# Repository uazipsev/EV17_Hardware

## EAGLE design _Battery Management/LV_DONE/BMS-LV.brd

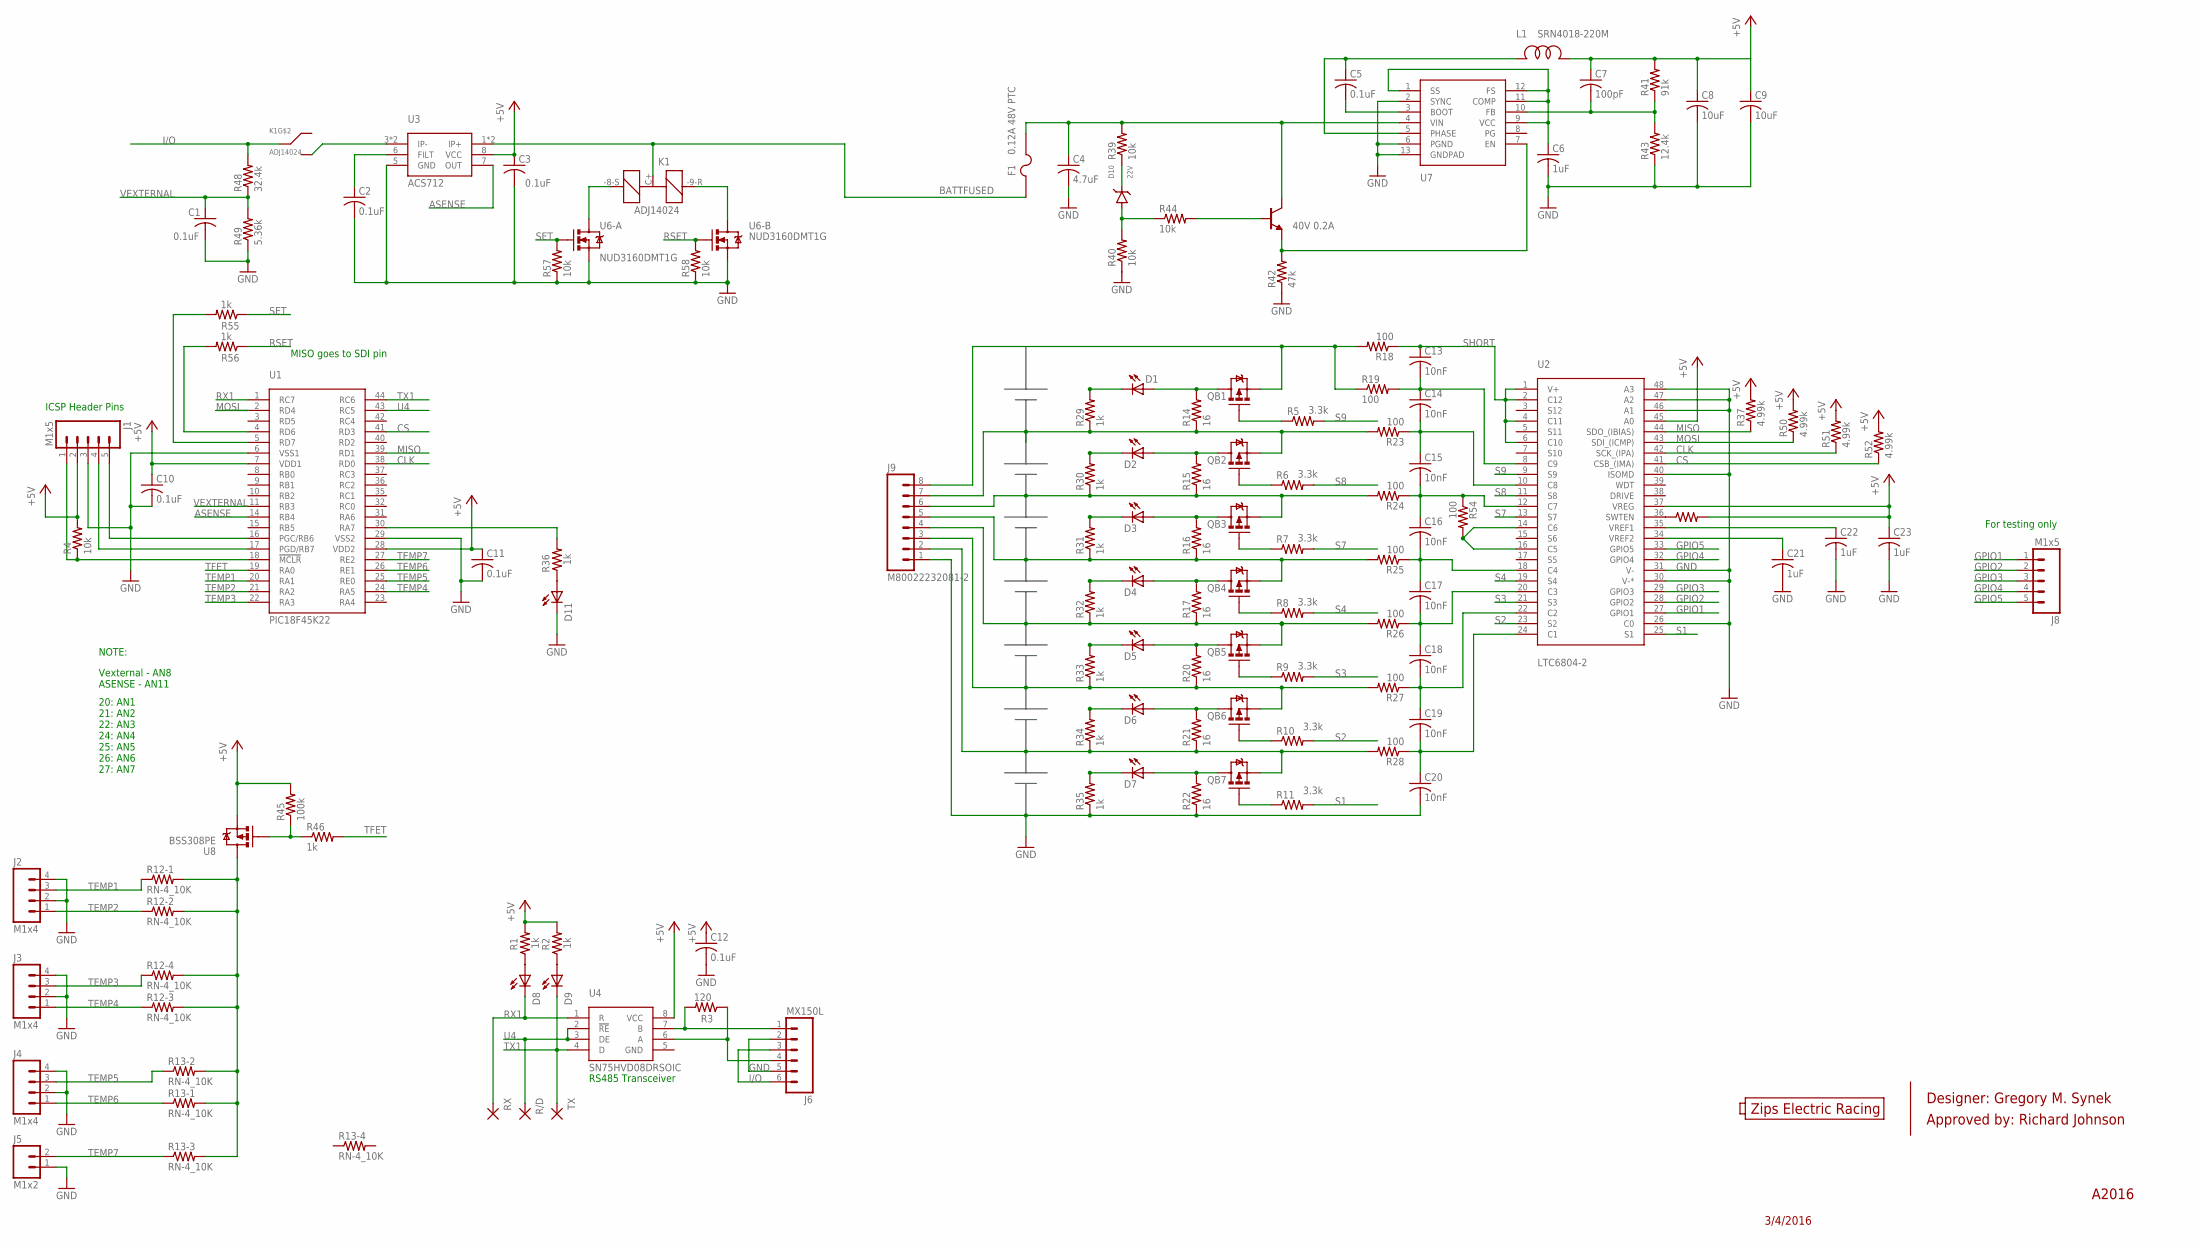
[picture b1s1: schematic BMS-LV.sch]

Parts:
C1, C3, C5, C10, C11, C12: 0.1uF; 0603
C2: 0.1uF; 0805
C4: 4.7uF; 1206@1
C6, C21, C22, C23: 1uF; 0805
C7: 100pF; 0603
C8, C9: 10uF; 1206@1
C13, C14, C15, C16, C17, C18, C19, C20: 10nF; 0603
D1, D2, D3, D4, D5, D6, D7, D9: LED_GREEN; CHIP_LED0805
D8, D11: LED_AMBER; CHIP_LED0805
D10: 22V; SOD-323
F1: 0.12A 48V PTC; 1206@1
J1, J8: M1x5; 5X.1
J2, J3, J4: M1x4; MOLEX_1X4
J5: M1x2; MOLEX-1X2
J6: MX150L; MOLEX-MX150L
J9: M80022232081-2; MOLEX-1X8-2
K1: ADJ14024
L1: SRN4018-220M; SRN4018
Q2: 40V 0.2A; SOT23
QB1, QB2, QB3, QB4, QB5, QB6, QB7: MOS-P_DMP2305U-7; SOT23
R1, R2, R29, R30, R31, R32, R33, R34, R35, R36, R55, R56: 1k; 0603
R3: 120; 0603
R4, R39, R40, R44, R57, R58: 10k; 0603
R5, R6, R7, R8, R9, R10, R11: 3.3k; 0805
R12, R13: RN-4_10K; MNR14
R14, R15, R16, R17, R20, R21, R22: 16; RR02J16RTB
R18, R19, R23, R24, R25, R26, R27, R28: 100; 0603
R37, R50, R51, R52: 4.99k; 0603
R41: 91k; 0805
R42: 47k; 0603
R43: 12.4k; 0603
R45: 100k; 0805
R46: 1k; 0805
R47: RES_0_1%; 0603
R48: 32.4k; 0603
R49: 5.36k; 0603
R54: 100; 0805
R/D: TPSMD; 0603
RX: TPSMD; 0603
TX: TPSMD; 0603
U1: PIC18F45K22; TQFP-44
U2: LTC6804-2; SSOP-48
U3: ACS712; SO-8
U4: SN75HVD08DRSOIC; SO-8
U6: NUD3160DMT1G; SC74-6
U7: ISL85415-FRZ-T7A; DFN-12
U8: BSS308PE; SOT23

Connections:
+5V: C3.1 (+), C7.1 (+), C8.1 (+), C9.1 (+), C10.1 (+), C11.1 (+), C12.1 (+), C23.1 (+), J1.2, L1.P$2, R1.2, R2.2, R4.2, R37.2, R41.2, R45.2, R47.2, R50.2, R51.2, R52.2, U1.7 (VDD1), U1.28 (VDD2), U2.37 (VREG), U2.45 (A0), U3.8 (VCC), U4.8 (VCC), U8.3 (S)
ASENSE: U1.14 (RB4), U3.7 (OUT)
BATTFUSED: F1.1, K1.C+ (-), U3.1 (IP+), U3.2 (IP+)
BATTPACK+: J9.8, QB1.3 (S), R18.2, R19.1
CLK: R51.1, U1.38 (RD0), U2.42 (SCK_(IPA))
CS: R52.1, U1.41 (RD3), U2.41 (CSB_(IMA))
GND: C1.2 (-), C2.2 (-), C3.2 (-), C4.2 (-), C6.2 (-), C8.2 (-), C9.2 (-), C10.2 (-), C11.2 (-), C12.2 (-), C20.2 (-), C21.2 (-), C22.2 (-), C23.2 (-), D11.C, J1.3, J2.2, J2.4, J3.2, J3.4, J4.2, J4.4, J5.1, J6.2, J6.5, J9.1, R22.P$1 (1), R35.1, R40.1, R42.1, R43.1, R49.1, R57.1, R58.1, U1.6 (VSS1), U1.29 (VSS2), U2.26 (C0), U2.30 (V-*), U2.31 (V-), U2.40 (ISOMD), U2.46 (A1), U2.47 (A2), U2.48 (A3), U3.5 (GND), U6.1 (S), U6.4 (S), U7.2 (SYNC), U7.6 (PGND), U7.13 (GNDPAD)
GPIO1: J8.1, U2.27 (GPIO1)
GPIO2: J8.2, U2.28 (GPIO2)
GPIO3: J8.3, U2.29 (GPIO3)
GPIO4: J8.4, U2.32 (GPIO4)
GPIO5: J8.5, U2.33 (GPIO5)
I/O: J6.3, J6.6, K1.C, R48.2
MISO: R37.1, U1.39 (RD1), U2.44 (SDO_(IBIAS))
MOSI: R50.1, U1.2 (RD4), U2.43 (SDI_(ICMP))
unnamed: D8.A, R1.1
unnamed: C13.2 (-), C14.1 (+), R19.2, U2.8 (C9)
unnamed: D9.A, R2.1
unnamed: C14.2 (-), C15.1 (+), R23.1, U2.10 (C8)
unnamed: D11.A, R36.1
unnamed: R55.2, U1.5 (RD7)
unnamed: K1.-8-S (+1), U6.6 (D)
unnamed: C15.2 (-), C16.1 (+), R24.1, R54.1, U2.12 (C7)
unnamed: J1.4, U1.17 (PGD/RB7)
unnamed: R45.1, R46.1, U8.1 (G)
unnamed: R47.1, U2.36 (SWTEN)
unnamed: D1.C, R29.2
unnamed: R36.2, U1.30 (RA7)
unnamed: K1.NO, U3.3 (IP-), U3.4 (IP-)
unnamed: C17.2 (-), C18.1 (+), R26.1, U2.20 (C3)
unnamed: R54.2, U2.14 (C6), U2.16 (C5)
unnamed: R56.2, U1.4 (RD6)
unnamed: K1.-9-R (+2), U6.3 (D)
unnamed: D2.C, R30.2
unnamed: C4.1 (+), F1.2, Q2.3, R39.2, U7.4 (VIN)
unnamed: C2.1 (+), U3.6 (FILT)
unnamed: D10.P$2 (A), R40.2, R44.1
unnamed: J6.4, R3.1, U4.6 (A)
unnamed: D10.P$1 (C), R39.1
unnamed: Q2.2, R42.2, U7.7 (EN)
unnamed: C5.2 (-), U7.3 (BOOT)
unnamed: J6.1, R3.2, U4.7 (B)
unnamed: J9.2, QB7.3 (S), R21.P$1 (1), R28.2, R34.1
unnamed: C6.1 (+), U7.1 (SS), U7.9 (VCC), U7.11 (COMP), U7.12 (FS)
unnamed: C5.1 (+), L1.P$1, U7.5 (PHASE)
unnamed: C18.2 (-), C19.1 (+), R27.1, U2.22 (C2)
unnamed: J1.5, U1.16 (PGC/RB6)
unnamed: C19.2 (-), C20.1 (+), R28.1, U2.24 (C1)
unnamed: D3.C, R31.2
unnamed: Q2.1, R44.2
unnamed: D4.C, R32.2
unnamed: D5.C, R33.2
unnamed: QB5.1 (G), R9.1
unnamed: D6.C, R34.2
unnamed: D5.A, QB5.2 (D), R20.P$2 (2)
unnamed: QB3.1 (G), R7.1
unnamed: J9.3, QB6.3 (S), R20.P$1 (1), R27.2, R33.1
unnamed: QB7.1 (G), R11.1
unnamed: J9.4, QB5.3 (S), R17.P$1 (1), R26.2, R32.1
unnamed: D7.A, QB7.2 (D), R22.P$2 (2)
unnamed: D7.C, R35.2
unnamed: QB6.1 (G), R10.1
unnamed: J1.1, R4.1, U1.18 (!MCLR)
unnamed: D6.A, QB6.2 (D), R21.P$2 (2)
unnamed: C7.2 (-), R41.1, R43.2, U7.10 (FB)
unnamed: J9.7, QB2.3 (S), R14.P$1 (1), R23.2, R29.1
unnamed: J9.6, QB3.3 (S), R15.P$1 (1), R24.2, R30.1
unnamed: J9.5, QB4.3 (S), R16.P$1 (1), R25.2, R31.1
unnamed: QB1.1 (G), R5.1
unnamed: D1.A, QB1.2 (D), R14.P$2 (2)
unnamed: QB2.1 (G), R6.1
unnamed: D2.A, QB2.2 (D), R15.P$2 (2)
unnamed: D3.A, QB3.2 (D), R16.P$2 (2)
unnamed: QB4.1 (G), R8.1
unnamed: D4.A, QB4.2 (D), R17.P$2 (2)
unnamed: R12.5 (2), R12.6 (2), R12.7 (2), R12.8 (2), R13.6 (2), R13.7 (2), R13.8 (2), U8.2 (D)
unnamed: C16.2 (-), C17.1 (+), R25.1, U2.18 (C4)
RSET: R56.1, R58.2, U6.5 (G)
RX1: D8.C, RX.1, RX.2, U1.1 (RC7), U4.1 (R)
S1: R11.2, U2.25 (S1)
S2: R10.2, U2.23 (S2)
S3: R9.2, U2.21 (S3)
S4: R8.2, U2.19 (S4)
S7: R7.2, U2.13 (S7)
S8: R6.2, U2.11 (S8)
S9: R5.2, U2.9 (S9)
SET: R55.1, R57.2, U6.2 (G)
SHORT: C13.1 (+), R18.1, U2.1 (V+), U2.2 (C12), U2.4 (C11), U2.6 (C10)
TEMP1: J2.3, R12.1, U1.20 (RA1)
TEMP2: J2.1, R12.2 (1), U1.21 (RA2)
TEMP3: J3.3, R12.4 (1), U1.22 (RA3)
TEMP4: J3.1, R12.3 (1), U1.24 (RA5)
TEMP5: J4.3, R13.2 (1), U1.25 (RE0)
TEMP6: J4.1, R13.1, U1.26 (RE1)
TEMP7: J5.2, R13.3 (1), U1.27 (RE2)
TFET: R46.2, U1.19 (RA0)
TX1: D9.C, TX.1, TX.2, U1.44 (RC6), U4.4 (D)
U4: R/D.1, R/D.2, U1.43 (RC5), U4.2 (!RE), U4.3 (DE)
VEXTERNAL: C1.1 (+), R48.1, R49.2, U1.11 (RB3)
VREF1: C22.1 (+), U2.35 (VREF1)
VREF2: C21.1 (+), U2.34 (VREF2)

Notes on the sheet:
RS485 Transceiver
ICSP Header Pins
For testing only
A2016
3/4/2016
Designer: Gregory M. Synek
Approved by: Richard Johnson
Zips Electric Racing
MISO goes to SDI pin
NOTE:
Vexternal - AN8 ASENSE - AN11
20: AN1 21: AN2 22: AN3 24: AN4 25: AN5 26: AN6 27: AN7

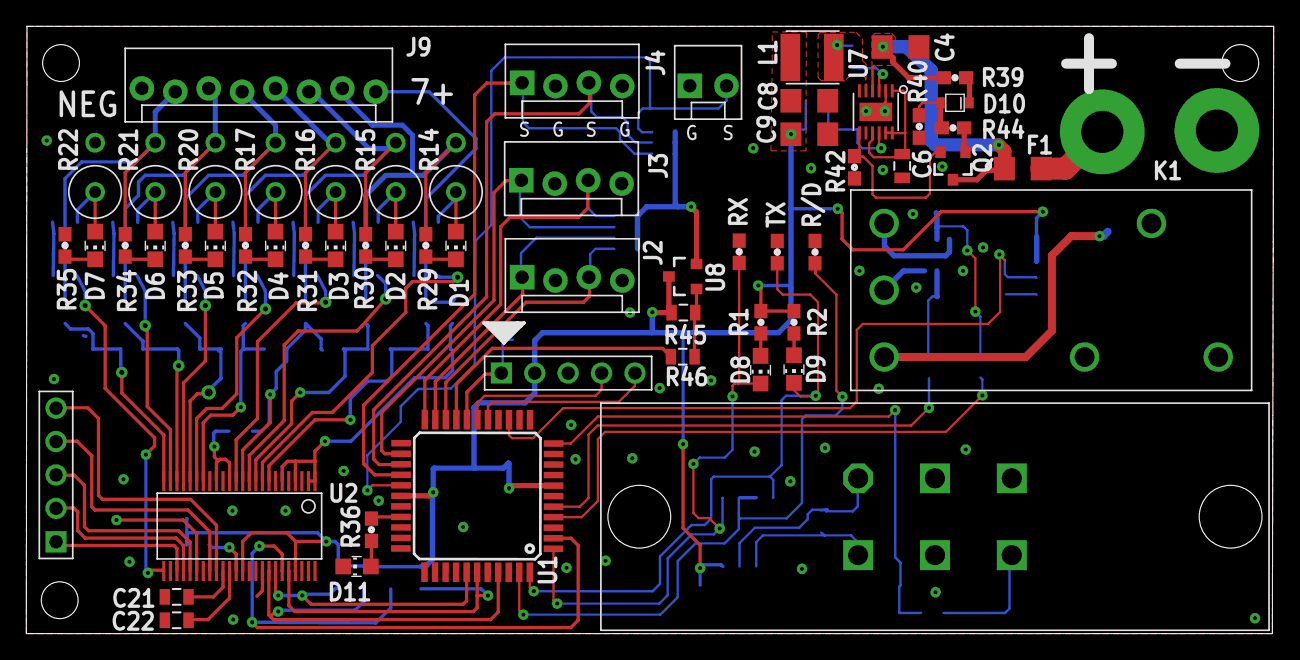
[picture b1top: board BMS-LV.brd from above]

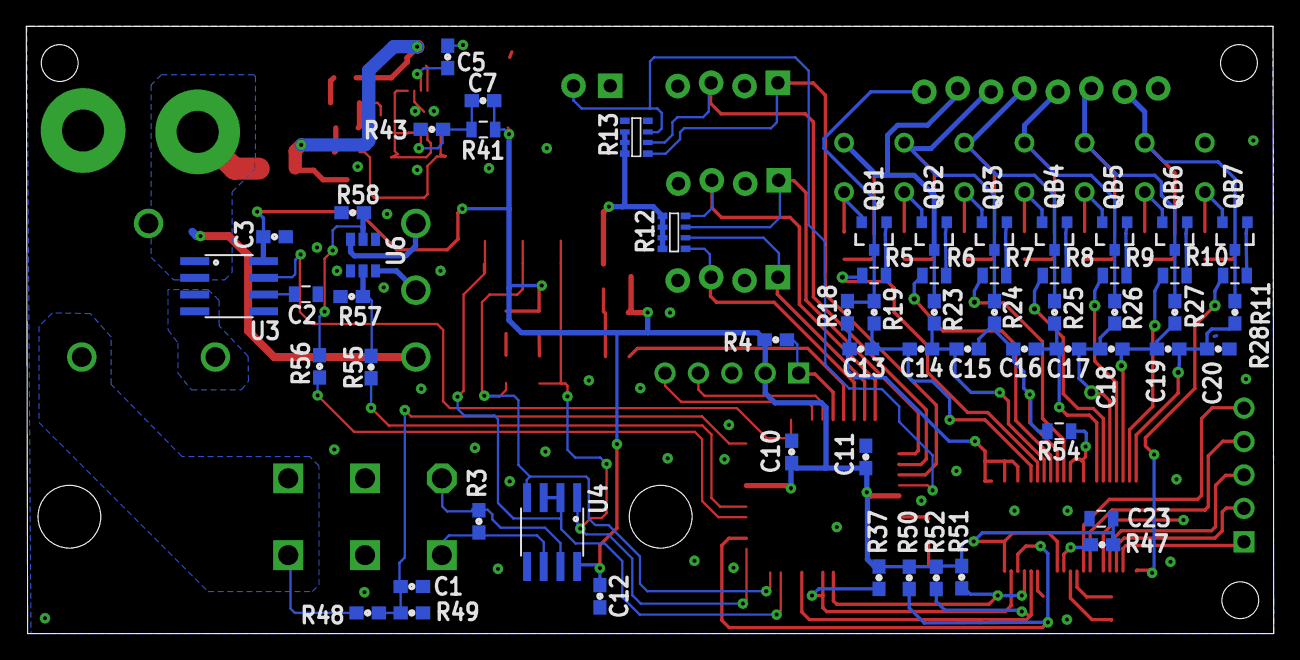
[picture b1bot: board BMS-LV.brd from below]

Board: 2 copper layers, 94.8 x 46.2 mm, 119 parts (60 on the bottom side), 101 nets.

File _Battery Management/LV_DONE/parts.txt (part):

Partlist

Exported from BMS-LV.brd at 4/22/2016 3:45 PM

EAGLE Version 7.5.0 Copyright (c) 1988-2015 CadSoft

Assembly variant: 

Part     Value            Package                  Library       Position (mil)        Orientation

C1       0.1uF            0603                     FSAE Electric (2977 980)            MR270.3
C2       0.1uF            0805                     FSAE Electric (2871 1539)           MR90
C3       0.1uF            0603                     FSAE Electric (2978 1684)           MR180
C4       4.7uF            1206@1                   FSAE Electric (2103 1093)           MR180
C5       0.1uF            0603                     FSAE Electric (2005.5 1315.5)       R0
C6       1uF              0805                     FSAE Electric (2228 1128)           MR270
C7       100pF            0603                     FSAE Electric (1878 1315.5)         R0
C8       10uF             1206@1                   FSAE Electric (1908 1038)           R0
C9       10uF             1206@1                   FSAE Electric (1908 938)            R0
C10      0.1uF            0603                     FSAE Electric (2436 1644)           MR0
C11      0.1uF            0603                     FSAE Electric (2324 1652)           MR270
C12      0.1uF            0603                     FSAE Electric (2553 599)            MR0
C13      10nF             0603                     FSAE Electric (1286 1662)           MR0
C14      10nF             0603                     FSAE Electric (1106 1662)           MR0
C15      10nF             0603                     FSAE Electric (966 1662)            MR0
C16      10nF             0603                     FSAE Electric (796 1662)            MR0
C17      10nF             0603                     FSAE Electric (666 1662)            MR0
C18      10nF             0603                     FSAE Electric (536 1662)            MR0
C19      10nF             0603                     FSAE Electric (366 1662)            MR0
C20      10nF             0603                     FSAE Electric (216 1662)            MR0
C21      1uF              0805                     FSAE Electric (770 1120)            MR90
C22      1uF              0805                     FSAE Electric (850 1118)            MR90
C23      1uF              0805                     FSAE Electric (1050 1142)           MR90
C24      10uF             1206@1                   FSAE Electric (1142 236)            MR0
C25      0.1uF            0603                     FSAE Electric (1436 363)            MR180
C26      0.1uF            0603                     FSAE Electric (1360 290)            R180
D1       LED_GREEN        CHIP_LED0805             FSAE Electric (1336 1972)           R180
D2       LED_GREEN        CHIP_LED0805             FSAE Electric (1156 1972)           R180
D3       LED_GREEN        CHIP_LED0805             FSAE Electric (976 1972)            R180
D4       LED_GREEN        CHIP_LED0805             FSAE Electric (796 1972)            R180
D5       LED_GREEN        CHIP_LED0805             FSAE Electric (616 1972)            R180
D6       LED_GREEN        CHIP_LED0805             FSAE Electric (436 1972)            R180
D7       LED_GREEN        CHIP_LED0805             FSAE Electric (256 1972)            R180
D8       LED_AMBER        CHIP_LED0805             FSAE Electric (2680 1040)           R180
D9       LED_GREEN        CHIP_LED0805             FSAE Electric (2750 1040)           R180
D10      22V              SOD-323                  FSAE Electric (2198 898)            R0
F1       0.12A 48V PTC    1206@1                   FSAE Electric (2482 842)            R90
F2       FUSE CLIPS       FUSECLIP-3550            FSAE Electric (2952 2258)           R270
J1       M1x5             5X.1                     FSAE Electric (2738 1614)           R270
J2       M1x4             MOLEX_1X4                FSAE Electric (1830 2350)           R90
J3       M1x4             MOLEX_1X4                FSAE Electric (1830 1930)           R90
J4       M1x4             MOLEX_1X4                FSAE Electric (1580 1930)           R90
J5       M1x2             MOLEX-1X2                FSAE Electric (1580 2250)           R90
J6       MX150L           MOLEX-MX150L             FSAE Electric (2720 350)            R0
J7       M2770166         1-770166-0               FSAE Electric (2382 2342)           R270
J8       M1x5             5X.1                     FSAE Electric (211 1327)            R90
J9       M80022232081-2   MOLEX-1X8-2              FSAE Electric (746 2442)            R0
K1       ADJ14024         ADJ14024                 FSAE Electric (3362 1850)           R270
L1       SRN4018-220M     SRN4018                  FSAE Electric (1918 1168)           R180
Q2       40V 0.2A         SOT23                    FSAE Electric (2168 998)            R90
Q3       BDX34C           TO-220                   FSAE Electric (1335 114)            R180
QB1      MOS-P_DMP2305U-7 SOT23                    FSAE Electric (1246 2002)           MR180
QB2      MOS-P_DMP2305U-7 SOT23                    FSAE Electric (1066 2002)           MR180
QB3      MOS-P_DMP2305U-7 SOT23                    FSAE Electric (886 2002)            MR180
QB4      MOS-P_DMP2305U-7 SOT23                    FSAE Electric (706 2002)            MR180
QB5      MOS-P_DMP2305U-7 SOT23                    FSAE Electric (526 2002)            MR180
QB6      MOS-P_DMP2305U-7 SOT23                    FSAE Electric (346 2002)            MR180
QB7      MOS-P_DMP2305U-7 SOT23                    FSAE Electric (166 2002)            MR180
R1       1k               0603                     FSAE Electric (2675 1170)           R90
R2       1k               0603                     FSAE Electric (2760 1170)           R90
R3       120              0603                     FSAE Electric (2605 460)            MR0
R4       10k              0603                     FSAE Electric (2817.5 1769.5)       MR270
R5       3.3k             0805                     FSAE Electric (1246 1882)           MR180
R6       3.3k             0805                     FSAE Electric (1066 1882)           MR180
R7       3.3k             0805                     FSAE Electric (886 1882)            MR180
R8       3.3k             0805                     FSAE Electric (706 1882)            MR180
R9       3.3k             0805                     FSAE Electric (526 1882)            MR180
R10      3.3k             0805                     FSAE Electric (346 1882)            MR180
R11      3.3k             0805                     FSAE Electric (166 1882)            MR180
R12      10k              MNR14                    FSAE Electric (1926 1672)           MR180
R13      10k              MNR14                    FSAE Electric (1686 1672)           MR0.1
R14      16               RR02J16RTB               FSAE Electric (1336 2132)           R270
R15      16               RR02J16RTB               FSAE Electric (1156 2132)           R270
R16      16               RR02J16RTB               FSAE Electric (976 2132)            R270
R17      16               RR02J16RTB               FSAE Electric (796 2132)            R270
R18      100              0603                     FSAE Electric (1326 1772)           MR90
R19      100              0603                     FSAE Electric (1246 1772)           MR270
R20      16               RR02J16RTB               FSAE Electric (616 2132)            R270
R21      16               RR02J16RTB               FSAE Electric (436 2132)            R270
R22      16               RR02J16RTB               FSAE Electric (256 2132)            R270
R23      100              0603                     FSAE Electric (1066 1772)           MR90
R24      100              0603                     FSAE Electric (886 1772)            MR90
R25      100              0603                     FSAE Electric (706 1772)            MR90
R26      100              0603                     FSAE Electric (526 1772)            MR90
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
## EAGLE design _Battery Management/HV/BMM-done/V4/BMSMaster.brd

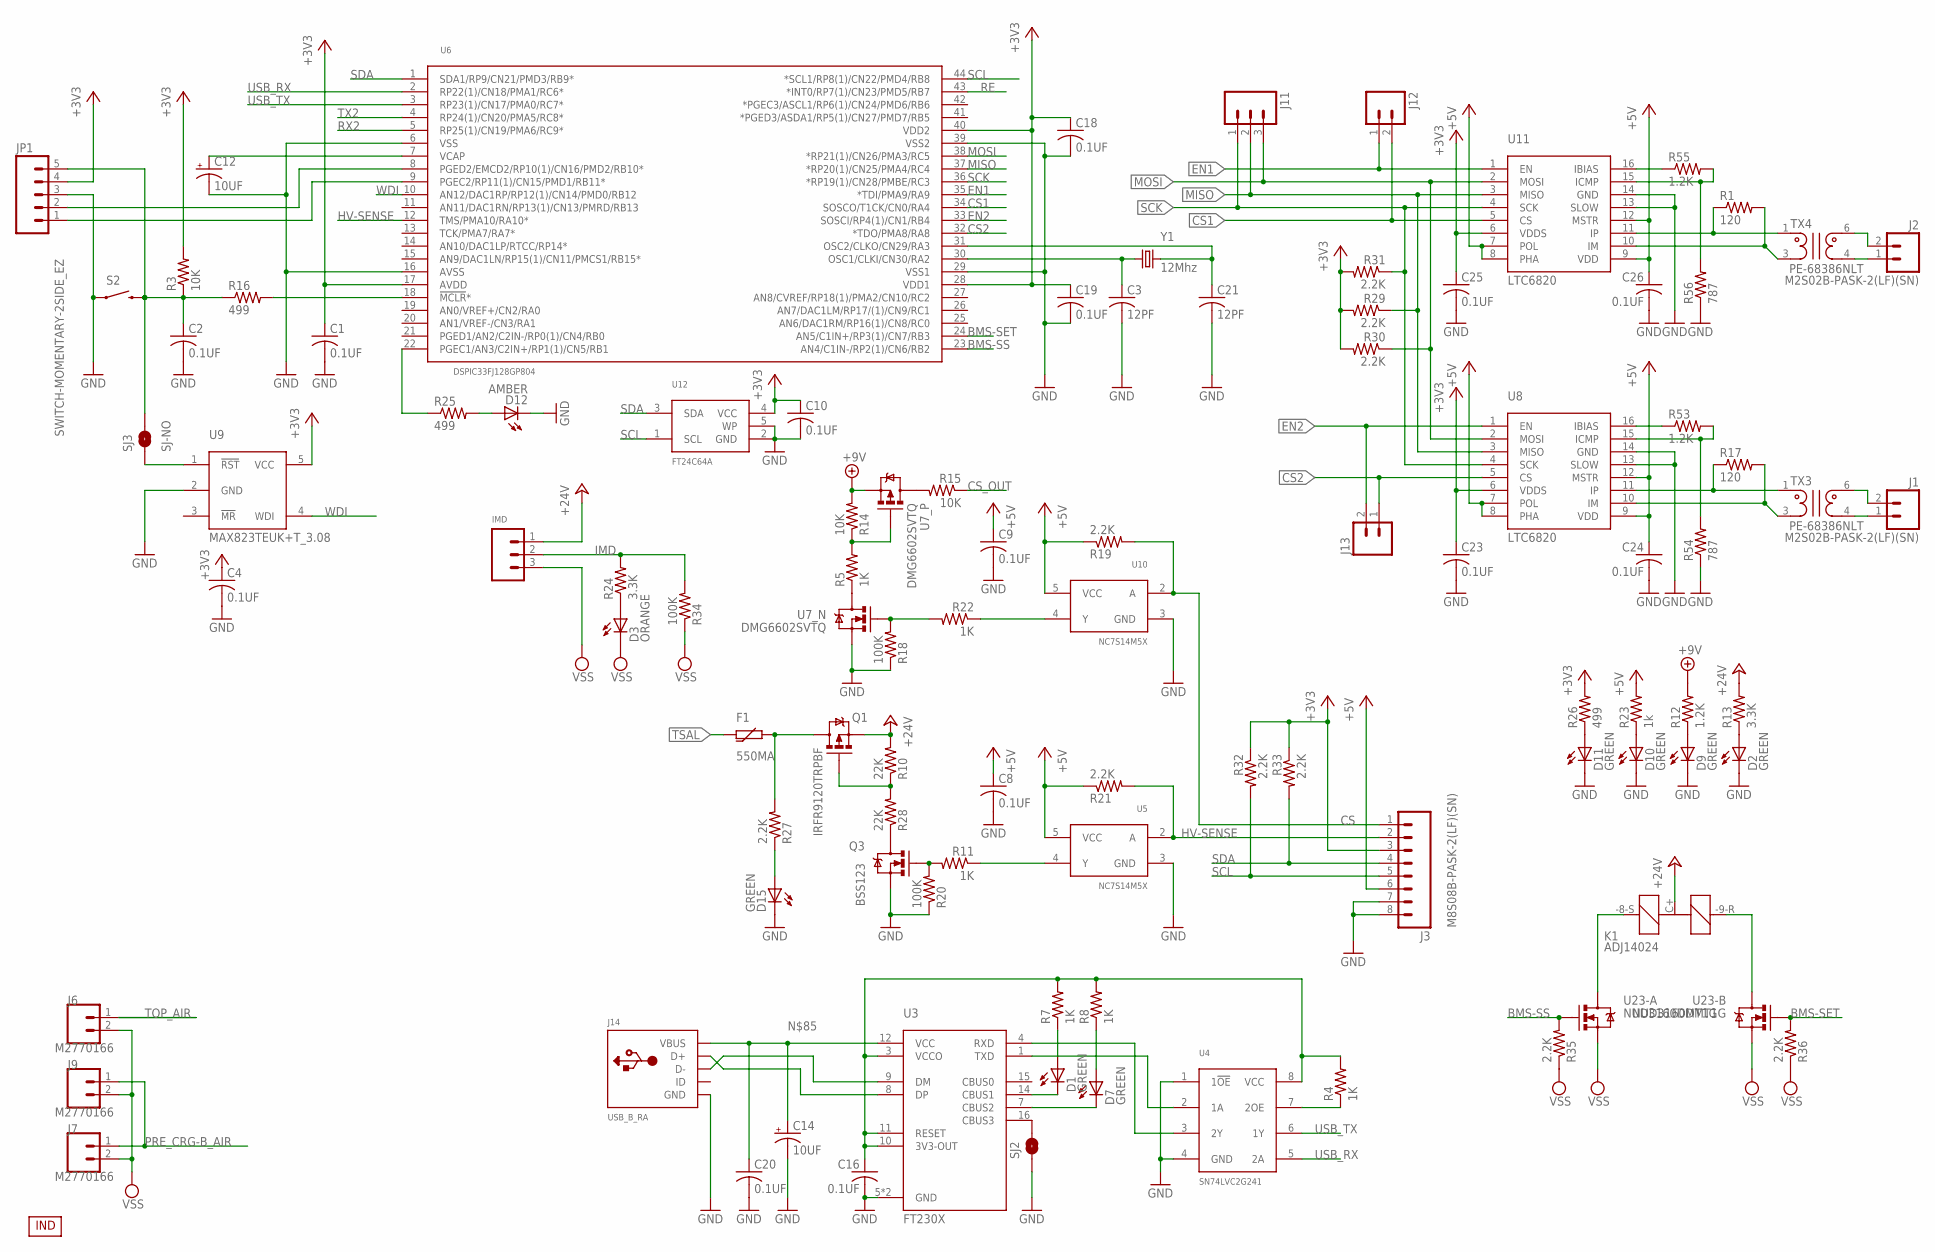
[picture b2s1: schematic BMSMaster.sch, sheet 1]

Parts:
C1, C2, C4, C8, C9, C10, C16, C18, C19, C20, C23, C24, C25, C26: 0.1UF; 0805
C3, C21: 12PF; 0805
C12, C14: 10UF; EIA3216-16V
D1, D2, D7, D9, D10, D11, D15: GREEN; CHIP_LED0805
D3: ORANGE; CHIP_LED0805
D12: AMBER; CHIP_LED0805
F1: 550MA; 2018
J1, J2: M2S02B-PASK-2(LF)(SN); S02B-PASK-2(LF)(SN)
J3: M8S08B-PASK-2(LF)(SN); S08B-PASK-2(LF)(SN)
J6, J7, J9: M2770166; 1-770166-0
J10: IMD; MOLEX-1X3
J11: M03LOCK_LONGPADS; 1X03_LOCK_LONGPADS
J12, J13: M02LOCK_LONGPADS; 1X02_LOCK_LONGPADS
J14: USB_B_RA; USB-B1HSW6
JP1: M05LOCK_LONGPADS; 1X05_LOCK_LONGPADS
K1: ADJ14024
Q1: IRFR9120TRPBF; DPAK
Q3: BSS123; SOT23
R1, R17: 120; 0805
R3, R14, R15: 10K; 0805
R4, R5, R7, R8, R11, R22: 1K; 0805
R10, R28: 22K; 0805
R12, R53, R55: 1.2K; 0805
R13, R24: 3.3K; 0805
R16, R25, R26: 499; 0805
R18, R20, R34: 100K; 0805
R19, R21, R27, R29, R30, R31, R32, R33, R35, R36: 2.2K; 0805
R23: 1k; 0805
R54, R56: 787; 0805
S2: SWITCH-MOMENTARY-2SIDE_EZ; TACTILE-PTH-SIDEEZ; PARTNO 3-1825910-5
SJ2: JUMPER-PAD-2-NOYES_SILK; PAD-JUMPER-2-NO_YES_SILK
SJ3: SJ-NO; SJ_2S-NO
TX3, TX4: PE-68386NLT
U3: FT230X; SSOP-16
U4: SN74LVC2G241; VFSOP-8
U5, U10: NC7S14M5X; SOT23-5
U6: DSPIC33FJ128GP804; TQFP-44
U7: DMG6602SVTQ; SOT23-6
U8, U11: LTC6820; MSOP-16
U9: MAX823TEUK+T_3.08; SOT23-5
U12: FT24C64A; SOT23-5
U23: NUD3160DMT1G; SC74-6
U$1: INDPK1; PICKIT-PIN-1
Y1: 12Mhz; CRYSTAL-SMD-5X3

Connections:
3V: C16.1 (+), R4.2, R7.2, R8.2, U3.3 (VCCO), U3.10 (3V3-OUT), U3.11 (RESET), U4.8 (VCC)
+3V3: C1.1 (+), C4.1 (+), C10.1 (+), C18.1 (+), C19.1 (+), C23.1 (+), C25.1 (+), J3.3, JP1.4, R3.2, R26.2, R29.2, R30.2, R31.2, R32.1, R33.1, U6.17 (AVDD), U6.28 (VDD1), U6.40 (VDD2), U8.6 (VDDS), U9.5 (VCC), U11.6 (VDDS), U12.4 (VCC); also elsewhere on the board
+5V: C8.1 (+), C9.1 (+), C24.1 (+), C26.1 (+), J3.6, R19.1, R21.1, R23.2, U5.5 (VCC), U8.7 (POL), U8.8 (PHA), U8.9 (VDD), U8.12 (MSTR), U10.5 (VCC), U11.7 (POL), U11.8 (PHA), U11.9 (VDD), U11.12 (MSTR); also elsewhere on the board
+9V: R12.2, R14.2, U7.2 (S); also elsewhere on the board
+24V: J10.1, K1.C+ (-), Q1.3 (S), R10.2, R13.2; also elsewhere on the board
BMS-SET: R36.2, U6.24 (AN5/C1IN+/RP3(1)/CN7/RB3), U23.5 (G)
BMS-SS: R35.2, U6.23 (AN4/C1IN-/RP2(1)/CN6/RB2), U23.2 (G)
CS: J3.1, R19.2, U10.2 (A)
CS1: J12.2, U6.34 (SOSCO/T1CK/CN0/RA4), U11.5 (CS)
CS2: J13.1, U6.32 (*TDO/PMA8/RA8), U8.5 (CS)
CS_OUT: R15.1; also elsewhere on the board
EN1: J12.1, U6.35 (*TDI/PMA9/RA9), U11.1 (EN)
EN2: J13.2, U6.33 (SOSCI/RP4(1)/CN1/RB4), U8.1 (EN)
GND: C1.2 (-), C2.2 (-), C3.2 (-), C4.2 (-), C8.2 (-), C9.2 (-), C10.2 (-), C12.C (-), C14.C (-), C16.2 (-), C18.2 (-), C19.2 (-), C20.2 (-), C21.2 (-), C23.2 (-), C24.2 (-), C25.2 (-), C26.2 (-), D2.C, D9.C, D10.C, D11.C, D12.C, D15.C, J3.7, J3.8, J14.4 (GND), JP1.3, Q3.2 (S), R18.1, R20.1, R54.1, R56.1, S2.1, SJ2.1, U3.5 (GND), U3.13 (GND), U4.1 (1!OE), U4.4 (GND), U5.3 (GND), U6.6 (VSS), U6.16 (AVSS), U6.29 (VSS1), U6.39 (VSS2), U7.5 (S), U8.13 (SLOW), U8.14 (GND), U9.2 (GND), U10.3 (GND), U11.13 (SLOW), U11.14 (GND), U12.2 (GND), U12.5 (WP); also elsewhere on the board
HV-SENSE: J3.2, R21.2, U5.2 (A), U6.12 (TMS/PMA10/RA10*)
IMD: J10.2, R24.2, R34.2; also elsewhere on the board
MISO: J11.2, R29.1, U6.37 (*RP20(1)/CN25/PMA4/RC4), U8.3 (MISO), U11.3 (MISO)
MOSI: J11.3, R30.1, U6.38 (*RP21(1)/CN26/PMA3/RC5), U8.2 (MOSI), U11.2 (MOSI)
unnamed: D12.A, R25.2
unnamed: C21.1 (+), U6.31 (OSC2/CLKO/CN29/RA3), Y1.3 (2)
unnamed: C3.1 (+), U6.30 (OSC1/CLKI/CN30/RA2), Y1.1
unnamed: SJ3.1, U9.1 (!RST)
unnamed: D7.A, R8.1
unnamed: D9.A, R12.1
unnamed: D7.C, U3.7 (CBUS2)
unnamed: D10.A, R23.1
unnamed: D1.C, U3.14 (CBUS1)
unnamed: Q1.1 (G), R10.1, R28.2
unnamed: D15.A, R27.1
unnamed: D11.A, R26.1
unnamed: U3.4 (RXD), U4.3 (2Y)
unnamed: U3.1 (TXD), U4.2 (1A)
unnamed: J14.2 (D-), U3.9 (DM)
unnamed: K1.-8-S (+1), U23.6 (D)
unnamed: J14.3 (D+), U3.8 (DP)
unnamed: R11.1, U5.4 (Y)
unnamed: D1.A, R7.1
unnamed: R53.1, U8.16 (IBIAS)
unnamed: R53.2, R54.2, U8.15 (ICMP)
unnamed: C12.A (+), U6.7 (VCAP)
unnamed: R55.1, U11.16 (IBIAS)
unnamed: R55.2, R56.2, U11.15 (ICMP)
unnamed: D2.A, R13.1
unnamed: J1.2, TX3.6
unnamed: J1.1, TX3.4
unnamed: R17.1, TX3.1, U8.11 (IP)
unnamed: R17.2, TX3.3, U8.10 (IM)
unnamed: R1.1, TX4.1, U11.11 (IP)
unnamed: R1.2, TX4.3, U11.10 (IM)
unnamed: R5.2, R14.1, U7.3 (G)
unnamed: R5.1, U7.6 (D)
unnamed: R22.1, U10.4 (Y)
unnamed: D3.A, R24.1
unnamed: SJ2.2, U3.16 (CBUS3)
unnamed: R25.1, U6.22 (PGEC1/AN3/C2IN+/RP1(1)/CN5/RB1)
unnamed: C2.1 (+), JP1.5, R3.1, R16.1, S2.2, SJ3.2
unnamed: R16.2, U6.18 (!MCLR!*)
unnamed: JP1.2, U6.8 (PGED2/EMCD2/RP10(1)/CN16/PMD2/RB10*)
unnamed: JP1.1, U6.9 (PGEC2/RP11(1)/CN15/PMD1/RB11*)
unnamed: R15.2, U7.4 (D)
unnamed: Q3.3 (D), R28.1
unnamed: F1.2, Q1.2 (D), R27.2
unnamed: J2.2, TX4.6
unnamed: K1.-9-R (+2), U23.3 (D)
unnamed: J2.1, TX4.4
unnamed: R4.1, U4.7 (2OE)
unnamed: C14.A (+), C20.1 (+), J14.1 (VBUS), U3.12 (VCC)
PRE_CRG-B_AIR: J7.1, J9.1; also elsewhere on the board
RE: U6.43 (*INT0/RP7(1)/CN23/PMD5/RB7); also elsewhere on the board
RX2: U6.5 (RP25(1)/CN19/PMA6/RC9*); also elsewhere on the board
SCK: J11.1, R31.1, U6.36 (*RP19(1)/CN28/PMBE/RC3), U8.4 (SCK), U11.4 (SCK)
SCL: J3.5, R32.2, U6.44 (*SCL1/RP8(1)/CN22/PMD4/RB8), U12.1 (SCL)
SDA: J3.4, R33.2, U6.1 (SDA1/RP9/CN21/PMD3/RB9*), U12.3 (SDA)
TOP_AIR: J6.1; also elsewhere on the board
TSAL: F1.1; also elsewhere on the board
TSAL_EN: Q3.1 (G), R11.2, R20.2
TSAL_EN1: R18.2, R22.2, U7.1 (G)
TX2: U6.4 (RP24(1)/CN20/PMA5/RC8*); also elsewhere on the board
USB_RX: U4.5 (2A), U6.2 (RP22(1)/CN18/PMA1/RC6*)
USB_TX: U4.6 (1Y), U6.3 (RP23(1)/CN17/PMA0/RC7*)
VSS: D3.C, J6.2, J7.2, J9.2, J10.3, R34.1, R35.1, R36.1, U23.1 (S), U23.4 (S); also elsewhere on the board
WDI: U6.10 (AN12/DAC1RP/RP12(1)/CN14/PMD0/RB12), U9.4 (WDI)

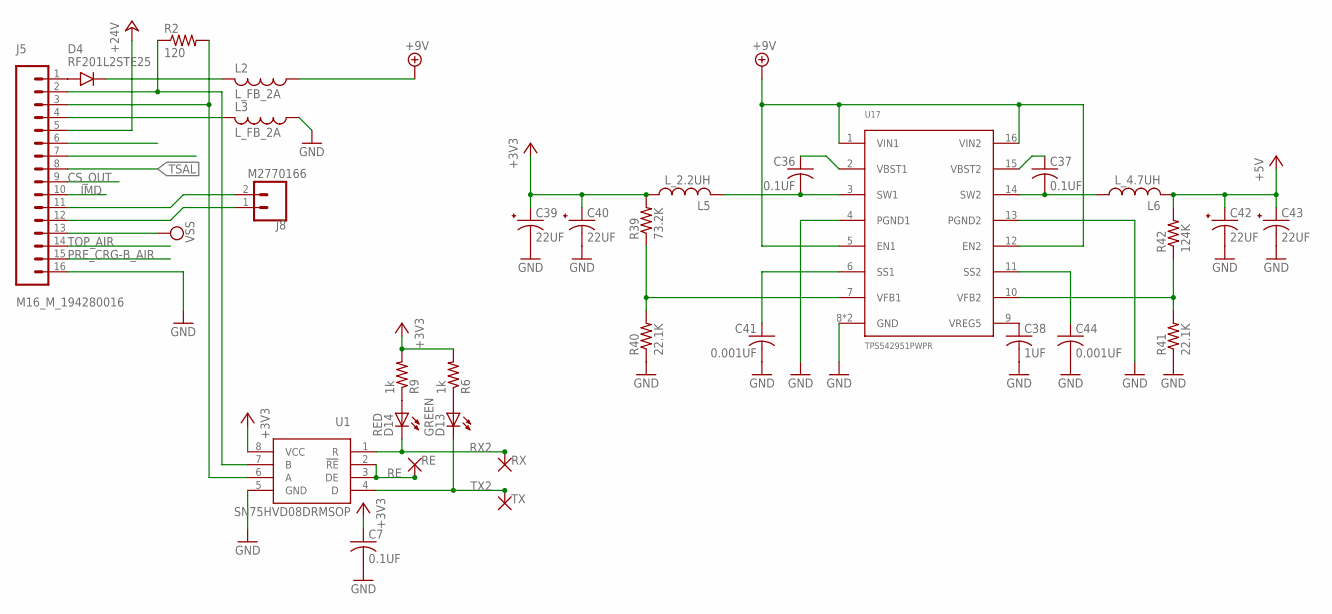
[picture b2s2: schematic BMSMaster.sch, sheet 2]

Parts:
C7: 0.1UF; 0805
C36, C37: 0.1UF; R0603
C38: 1UF; R0603
C39, C40, C42, C43: 22UF; EIA7343
C41, C44: 0.001UF; R0603
D4: RF201L2STE25; SMA
D13: GREEN; CHIP_LED0805
D14: RED; CHIP_LED0805
J5: M16_M_194280016; 19428-0016
J8: M2770166; 1-770166-0
L2, L3: L_FB_2A; 0805
L5: L_2.2UH; LQH43
L6: L_4.7UH; LQH43
R2: 120; 0805
R6, R9: 1k; 0805
R39: 73.2K; R0805
R40, R41: 22.1K; R0805
R42: 124K; R0805
RE: TP; 0603
RX: TP; 0603
TX: TP; 0603
U1: SN75HVD08DRMSOP; MSOP-8
U17: TPS542951PWPR; TSSOP-16

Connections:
+3V3: C7.1 (+), C39.+, C40.+, L5.1, R6.2, R9.2, R39.2, U1.8 (VCC); also elsewhere on the board
+5V: C42.+, C43.+, L6.2, R42.2; also elsewhere on the board
+9V: L2.1, U17.1 (VIN1), U17.5 (EN1), U17.12 (EN2), U17.16 (VIN2); also elsewhere on the board
+24V: J5.5; also elsewhere on the board
CS_OUT: J5.9; also elsewhere on the board
GND: C7.2 (-), C38.2, C39.-, C40.-, C41.2, C42.-, C43.-, C44.2, J5.16, L3.1, R40.1, R41.1, U1.5 (GND), U17.4 (PGND1), U17.8 (GND), U17.13 (PGND2), U17.EP (GND); also elsewhere on the board
IMD: J5.10; also elsewhere on the board
INTERLOCK_IN: J5.11, J8.2
INTERLOCK_OUT: J5.12, J8.1
unnamed: D13.A, R6.1
unnamed: D14.A, R9.1
unnamed: J5.2, R2.1, U1.7 (B)
unnamed: J5.3, R2.2, U1.6 (A)
unnamed: C44.1, U17.11 (SS2)
unnamed: J5.4, L3.2
unnamed: D4.A, J5.1
unnamed: D4.C, L2.2
unnamed: C36.1, U17.2 (VBST1)
unnamed: C36.2, L5.2, U17.3 (SW1)
unnamed: C37.1, U17.15 (VBST2)
unnamed: C37.2, L6.1, U17.14 (SW2)
unnamed: C38.1, U17.9 (VREG5)
unnamed: R39.1, R40.2, U17.7 (VFB1)
unnamed: C41.1, U17.6 (SS1)
unnamed: R41.2, R42.1, U17.10 (VFB2)
PRE_CRG-B_AIR: J5.15; also elsewhere on the board
RE: RE.1, RE.2, U1.2 (!RE), U1.3 (DE); also elsewhere on the board
RX2: D14.C, RX.1, RX.2, U1.1 (R); also elsewhere on the board
TOP_AIR: J5.14; also elsewhere on the board
TSAL: J5.8; also elsewhere on the board
TX2: D13.C, TX.1, TX.2, U1.4 (D); also elsewhere on the board
VSS: J5.13; also elsewhere on the board

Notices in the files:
parts and their libraries:
SparkFun-Passives: Licensing: CC v3.0 Share-Alike You are welcome to use this library for commercial purposes.
SparkFun-Connectors: Licensing: Creative Commons ShareAlike 4.0 International - https://creativecommons.org/licenses/by-sa/4.0
SparkFun-Aesthetics: Released under the Creative Commons
